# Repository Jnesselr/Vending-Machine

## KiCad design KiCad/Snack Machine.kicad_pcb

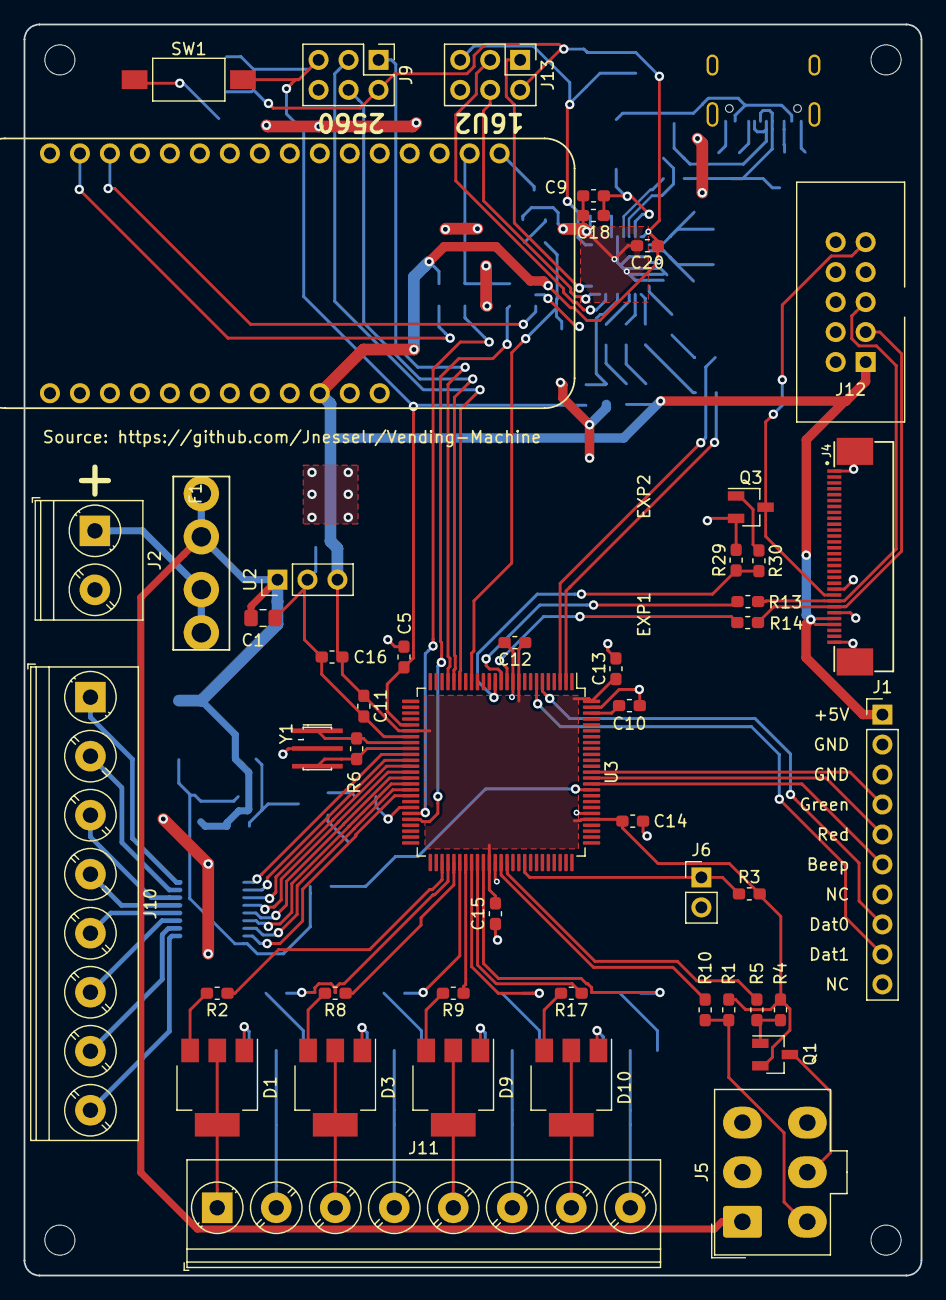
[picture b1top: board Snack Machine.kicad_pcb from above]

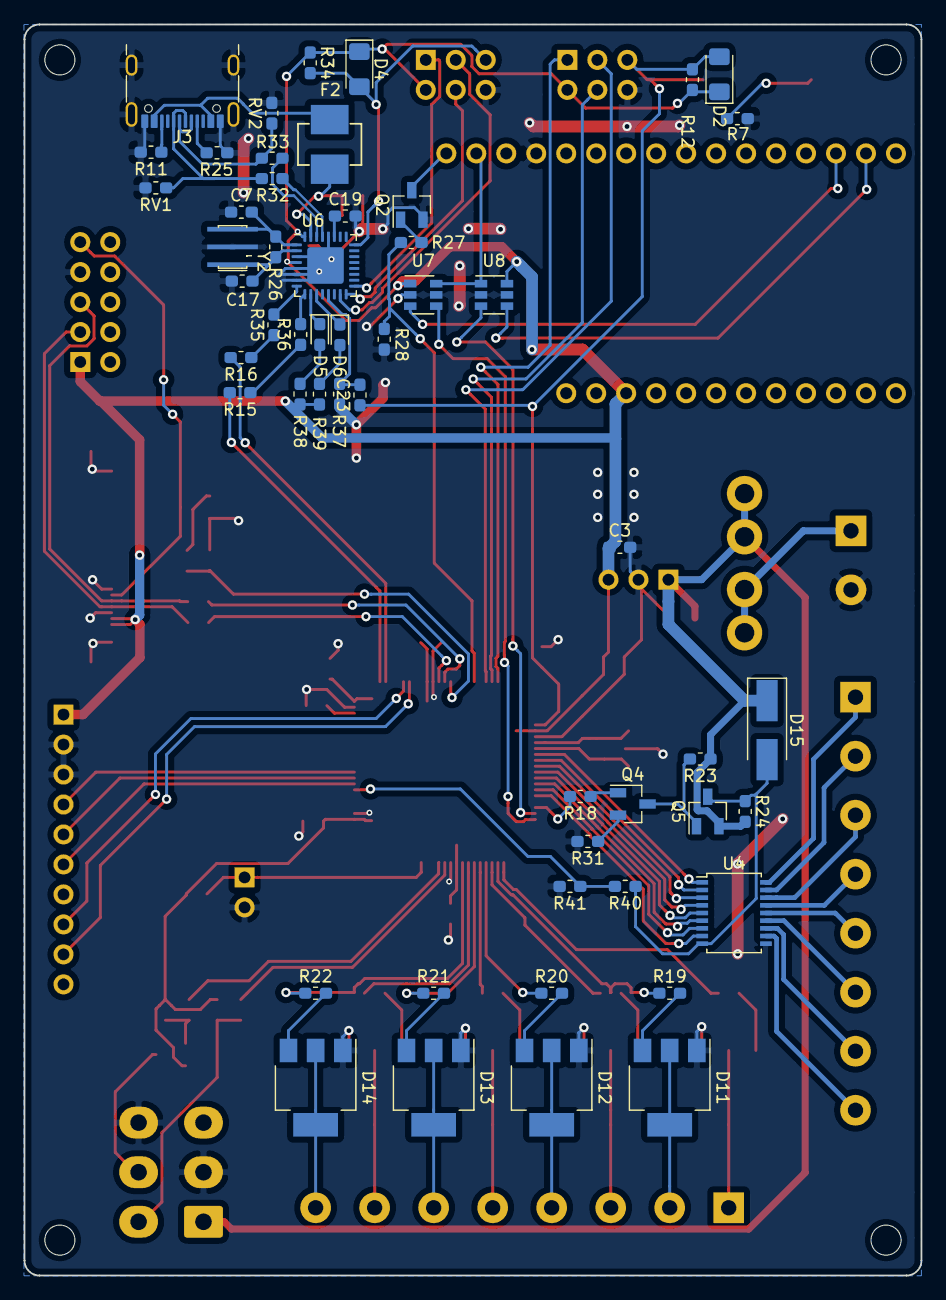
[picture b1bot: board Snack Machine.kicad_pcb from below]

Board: 2 copper layers, 76.0 x 106.0 mm, 105 parts (53 on the bottom side), 110 nets.

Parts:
C1: 2.2uF 35V; C_0805_2012Metric_Pad1.15x1.40mm_HandSolder
C3: 10uF 10V; C_0603_1608Metric_Pad1.05x0.95mm_HandSolder
C5, C7, C17: 22pF; C_0603_1608Metric_Pad1.05x0.95mm_HandSolder
C9, C10, C11, C12, C13, C14, C15, C23: 100nF; C_0603_1608Metric_Pad1.05x0.95mm_HandSolder
C16, C18, C19, C20: 1uF; C_0603_1608Metric_Pad1.05x0.95mm_HandSolder
D1, D3, D9, D10, D11, D12, D13, D14: Q_TRIAC_A1A2G; SOT-223-3_TabPin2
D2, D4: D; D_1206_3216Metric_Pad1.42x1.75mm_HandSolder
D5, D6: YELLOW; LED_0603_1608Metric_Pad1.05x0.95mm_HandSolder
D15: S1GTR; D_SMA_Handsoldering
F1: 1A; Keystone_3544-2
F2: 500mA; MF-MSMF050-2
J1: RFID_CONNECTOR; CONN_HEADER_VERT_10POS_2.54MM
J2: Power Screw Terminal; TerminalBlock_Phoenix_PT-1,5-2-5.0-H_1x02_P5.00mm_Horizontal
J3: USB_C_Receptacle_USB2.0; USB_C_Receptacle_HRO_TYPE-C-31-M-12
J4: V2 Display Ribbon Cable; FPC30
J5: MDB; Molex_Mini-Fit_Jr_5566-06A_2x03_P4.20mm_Vertical
J6: Conn_01x02; CONN_HEADER_VERT_2POS_2.54MM
J9, J13: AVR-ISP-6; PinHeader_2x03_P2.54mm_Vertical
J10: Row Screw Terminal; TerminalBlock_Phoenix_PT-1,5-8-5.0-H_1x08_P5.00mm_Horizontal
J11: Column Screw Terminal; TerminalBlock_Phoenix_PT-1,5-8-5.0-H_1x08_P5.00mm_Horizontal
J12: Display Serial Header; PinHeader_2x05_P2.54mm_Vertical
Q1, Q5: P-CH 30V 3.8A; SOT-23_Handsoldering_Lite
Q2, Q3, Q4: MMBT3904; SOT-23_Handsoldering_Lite
R1, R2, R5, R7, R8, R9, R17, R18, R19, R20, R21, R22, R35, R36, R37, R38, R39: 1k; R_0603_1608Metric_Pad1.05x0.95mm_HandSolder
R3, R4, R12, R23, R24, R34, R41: 10k; R_0603_1608Metric_Pad1.05x0.95mm_HandSolder
R6, R26: 1M; R_0603_1608Metric_Pad1.05x0.95mm_HandSolder
R10, R13, R14, R15, R16: 0R; R_0603_1608Metric_Pad1.05x0.95mm_HandSolder
R11, R25: 5k1; R_0603_1608Metric_Pad1.05x0.95mm_HandSolder
R27, R28, R29, R30, R31: 4.7k; R_0603_1608Metric_Pad1.05x0.95mm_HandSolder
R32, R33: 22R; R_0603_1608Metric_Pad1.05x0.95mm_HandSolder
R40: 47k; R_0603_1608Metric_Pad1.05x0.95mm_HandSolder
RV1, RV2: CG0603MLC; R_0603_1608Metric_Pad1.05x0.95mm_HandSolder
SW1: SW_SPST; SW_SPST_FSMSM
TH1, TH2, TH3, TH4: tooling_hole; tooling_hole_2.55
U2: MEZD71202A-G; mEZD71201A
U3: ATmega2560-16AU; TQFP-100_14x14mm_P0.5mm
U4: TBD62783A; SSOP-18_4.4x6.5mm_P0.65mm
U5: Huzzah32; HUZZAH32
U6: ATmega16U2-MU; QFN-32-1EP_5x5mm_P0.5mm_EP3.1x3.1mm
U7, U8: SN74LVC1T45DBV; SOT-23-6
Y1, Y2: 16MHz; Resonator_SMD_ECS-CR2-16.00-B-TR

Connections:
+3V3: U5.27, U7.6, U8.1
+5V: C3.1, C11.1, C12.1, C13.1, C14.1, C15.1, C16.1, C20.1, D2.1, D4.1, J1.1, J4.26, J4.27, J9.2, J12.1, J13.2, Q1.2, R1.2, R3.2, R4.2, R12.2, R34.1, R38.2, R39.2, U2.3, U3.10, U3.31, U3.61, U3.80, U3.100, U5.3, U6.4, U6.32, U7.1, U8.6
+24V: C1.1, D15.1, F1.1, J5.1, Q5.2, R23.1, R24.2, U2.1
/4D_Display/DISPLAY_RX: J4.23, J12.5, R13.2
/4D_Display/DISPLAY_TX: J4.24, J12.3, R14.2
/4D_Display/RESET: J4.22, J12.9, Q3.3
/DISPLAY_RX_MEGA_TX: R13.1, U3.13
/DISPLAY_TX_MEGA_RX: R14.1, U3.12
/DOOR_SW: J6.1, R3.1, U3.67
/HUZZAH_RX_MEGA_TX: U3.46, U7.4
/HUZZAH_TX_MEGA_RX: U3.45, U8.3
/MDB_RX: Q1.1, R4.1, R5.1
/MDB_RX_MEGA_TX: R5.2, U3.64
/MDB_TX: J5.4, R1.1, R10.1
/MDB_TX_MEGA_RX: R10.2, U3.63
/MISO: J9.1, U3.22
/MOSI: J9.4, U3.21
/MOTORS_ENABLE: R18.2, U3.44
/MOTOR_SENSE: R40.2, R41.1, U3.85
/MotorPower/col_1_motor: D1.2, J11.1
/MotorPower/col_2_motor: D11.2, J11.2
/MotorPower/col_3_motor: D3.2, J11.3
/MotorPower/col_4_motor: D12.2, J11.4
/MotorPower/col_5_motor: D9.2, J11.5
/MotorPower/col_6_motor: D13.2, J11.6
/MotorPower/col_7_motor: D10.2, J11.7
/MotorPower/col_8_motor: D14.2, J11.8
/MotorPower/row_a_motor: J10.1, U4.18
/MotorPower/row_b_motor: J10.2, U4.17
/MotorPower/row_c_motor: J10.3, U4.16
/MotorPower/row_d_motor: J10.4, U4.15
/MotorPower/row_e_motor: J10.5, U4.14
/MotorPower/row_f_motor: J10.6, U4.13
/MotorPower/row_g_motor: J10.7, U4.12
/MotorPower/row_h_motor: J10.8, U4.11
/RESET_DISPLAY: R29.1, R30.2, U3.14
/RESET_HUZZAH: R27.2, R28.1, U3.18
/RFID_BEEP_CTRL: J1.6, U3.86
/RFID_DATA_0: J1.8, U3.6
/RFID_DATA_1: J1.9, U3.7
/RFID_GREEN_LED: J1.4, U3.88
/RFID_RED_LED: J1.5, U3.87
/SCK: J9.3, U3.20
/USB_Serial/DTR: C23.2, R37.2, U6.13
/USB_Serial/MICRO_D+: R32.1, U6.29
/USB_Serial/MICRO_D-: R33.1, U6.30
/USB_Serial/MISO2: J13.1, U6.17
/USB_Serial/MOSI2: J13.4, U6.16
/USB_Serial/RXL: D5.1, U6.10
/USB_Serial/RX_USB: R16.1, R35.1
/USB_Serial/SCK2: J13.3, U6.15
/USB_Serial/TXL: D6.1, U6.11
/USB_Serial/TX_USB: R15.1, R36.1
/USB_Serial/USBVCC: C9.1, C18.1, F2.1, U6.31
/USB_Serial/USB_D+: J3.A6, J3.B6, R32.2, RV1.1
/USB_Serial/USB_D-: J3.A7, J3.B7, R33.2, RV2.1
/USB_Serial/XVCC: F2.2, J3.A4, J3.B4
/USB_Serial/~RESET2: D4.2, J13.5, R34.2, U6.24
/XTAL1: R6.1, U3.34, Y1.3
/XTAL2: R6.2, U3.33, Y1.1
/c1: R2.1, U3.53
/c2: R19.1, U3.54
/c3: R8.1, U3.55
/c4: R20.1, U3.56
/c5: R9.1, U3.57
/c6: R21.1, U3.58
/c7: R17.1, U3.59
/c8: R22.1, U3.60
/r1: U3.35, U4.1
/r2: U3.36, U4.2
/r3: U3.37, U4.3
/r4: U3.38, U4.4
/r5: U3.39, U4.5
/r6: U3.40, U4.6
/r7: U3.41, U4.7
/r8: U3.42, U4.8
/~RESET: C5.1, C23.1, D2.2, J9.5, R12.1, SW1.2, U3.30
GND: C1.2, C3.2, C5.2, C7.1, C9.2, C10.2, C11.2, C12.2, C13.2, C14.2, C15.2, C16.2, C17.1, C18.2, C19.2, C20.2, D1.1, D3.1, D9.1, D10.1, D11.1, D12.1, D13.1, D14.1, J1.2, J1.3, J2.2, J3.A1, J3.B1, J3.S1, J4.1, J4.21, J4.25, J4.30, J4.MP, J5.2, J5.6, J6.2, J9.6, J12.7, J13.6, Q2.2, Q3.2, R7.1, R11.2, R25.2, R28.2, R29.2, R31.2, R37.1, R41.2, RV1.2, RV2.2, U2.2, U3.11, U3.32, U3.62, U3.81, U3.99, U4.10, U5.25, U6.3, U6.5, U6.6, U6.7, U6.28, U6.33, U7.2, U7.5, U8.2, U8.5, Y1.2, Y2.2
unnamed: C7.2, R26.1, U6.1, Y2.3
unnamed: C10.1, U3.98
unnamed: C17.2, R26.2, U6.2, Y2.1
unnamed: C19.1, U6.27
unnamed: D1.3, R2.2
unnamed: D3.3, R8.2
unnamed: D5.2, R38.1
unnamed: D6.2, R39.1
unnamed: D9.3, R9.2
unnamed: D10.3, R17.2
unnamed: D11.3, R19.2
unnamed: D12.3, R20.2
unnamed: D13.3, R21.2
unnamed: D14.3, R22.2
unnamed: D15.2, Q5.3, R24.1, R40.1, U4.9
unnamed: F1.2, J2.1
unnamed: J3.A5, R25.1
unnamed: J3.B5, R11.1
unnamed: J5.5, Q1.3
unnamed: Q2.1, R27.1
unnamed: Q2.3, U5.28
unnamed: Q3.1, R30.1
unnamed: Q4.1, R18.1
unnamed: Q4.2, R31.1
unnamed: Q4.3, Q5.1, R23.2
unnamed: R7.2, SW1.1
unnamed: R15.2, U3.2
unnamed: R16.2, U3.3
unnamed: R35.2, U6.8
unnamed: R36.2, U6.9
unnamed: U5.14, U8.4
unnamed: U5.15, U7.3

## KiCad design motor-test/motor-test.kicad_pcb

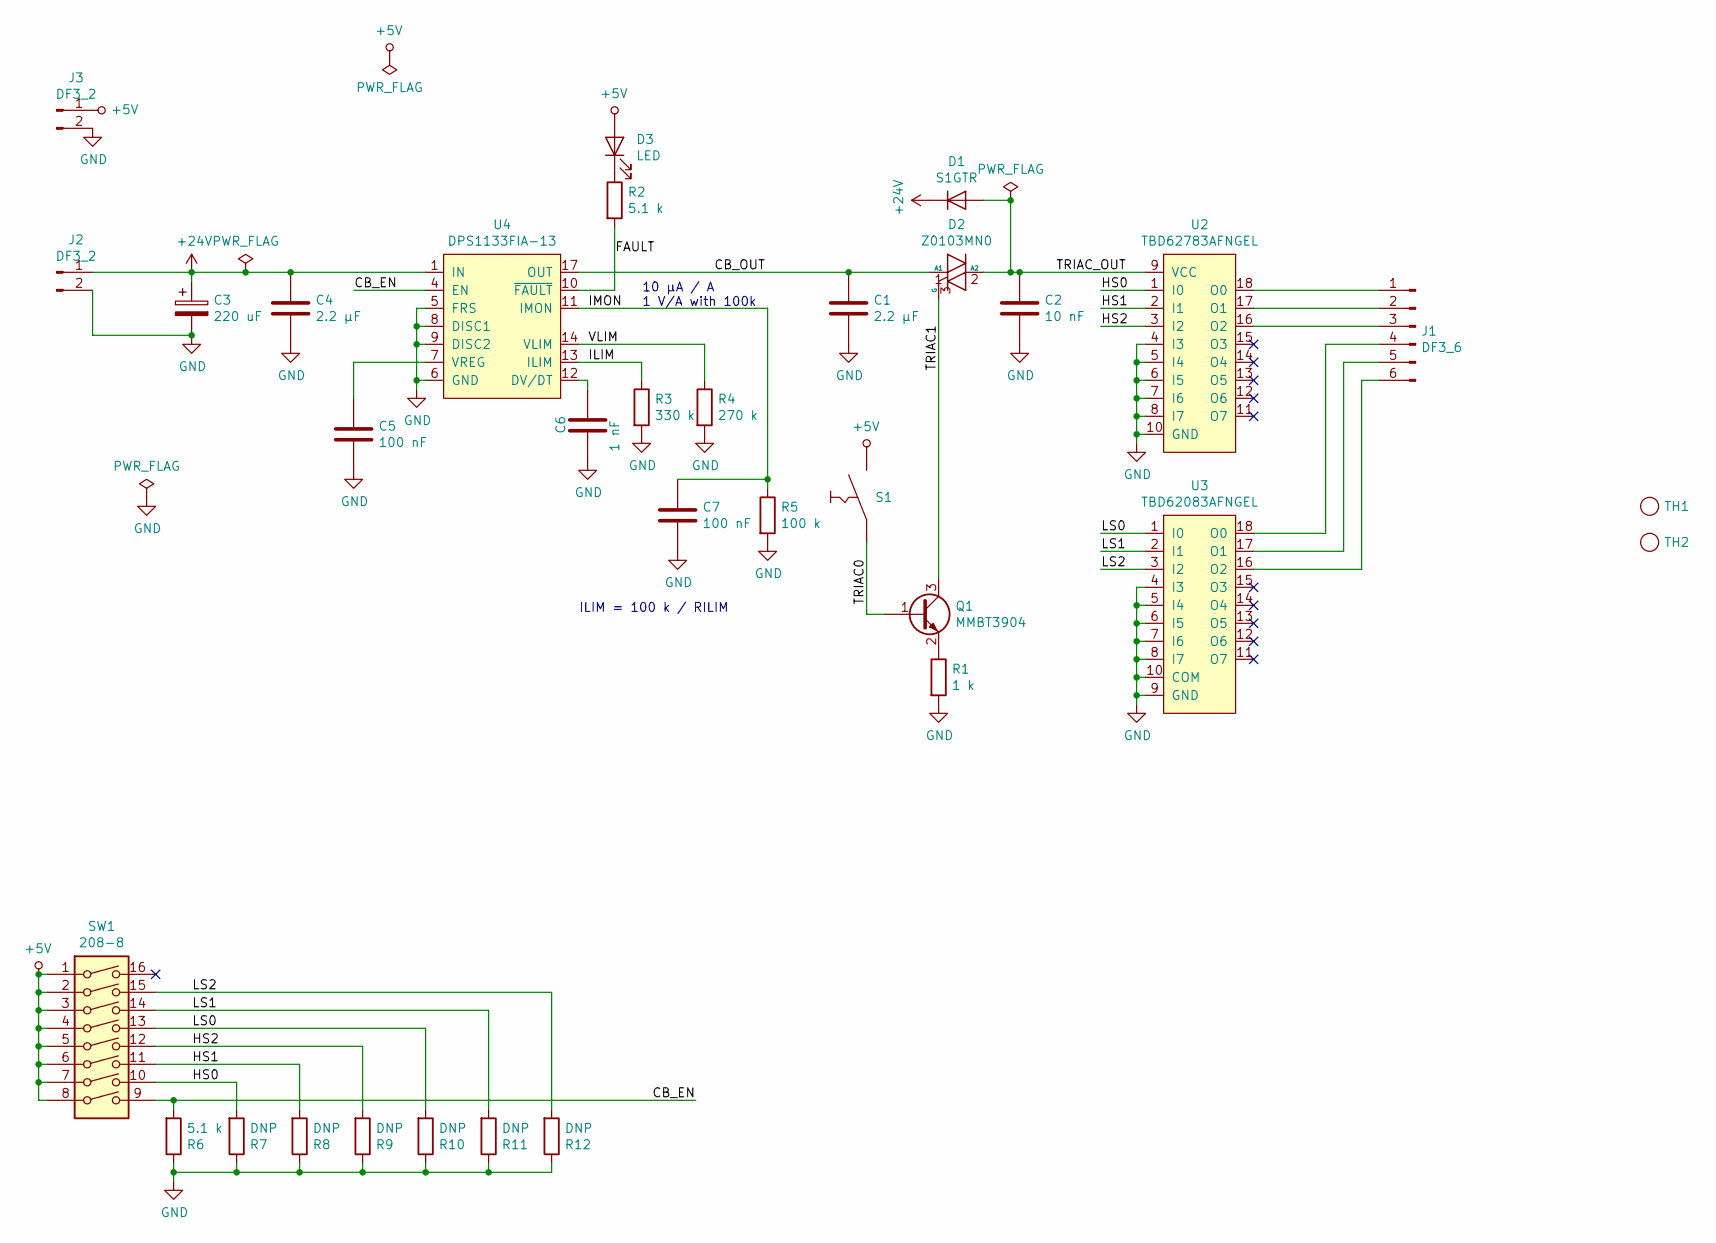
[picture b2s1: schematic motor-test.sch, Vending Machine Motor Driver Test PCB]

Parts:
C1, C4: 2.2 μF; C_0603_1608Metric
C2: 10 nF; C_0603_1608Metric
C3: 220 uF; CP_Radial_D10.0mm_P5.00mm
C5, C7: 100 nF; C_0603_1608Metric
C6: 1 nF; C_0603_1608Metric
D1: S1GTR; D_SMA
D2: Z0103MN0; SOT-223-3_TabPin2
D3: LED; LED_0603_1608Metric
J1: DF3_6
J2, J3: DF3_2
Q1: MMBT3904; SOT-23
R1: 1 k; R_0603_1608Metric
R2, R6: 5.1 k; R_0603_1608Metric
R3: 330 k; R_0603_1608Metric
R4: 270 k; R_0603_1608Metric
R5: 100 k; R_0603_1608Metric
R7, R8, R9, R10, R11, R12: DNP; R_0603_1608Metric
S1: 147873-1; PB_3.5x6
SW1: 208-8; DIP-16_W7.62mm
TH1, TH2: tooling_hole; tooling_hole_2.55
U2: TBD62783AFNGEL; SSOP-18_4.4x6.5mm_P0.65mm
U3: TBD62083AFNGEL; SSOP-18_4.4x6.5mm_P0.65mm
U4: DPS1133FIA-13; QFN-17-Diodes1

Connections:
+5V: D3.2 (A), J3.1, S1.2, SW1.1, SW1.2, SW1.3, SW1.4, SW1.5, SW1.6, SW1.7, SW1.8
+24V: C3.1, C4.1, D1.1 (K), J2.1, U4.1 (IN)
/CB_EN: R6.2, SW1.9, U4.4 (EN)
/CB_OUT: C1.1, D2.1 (A1), U4.17 (OUT)
/FAULT: R2.2, U4.10 (~FAULT)
/HS0: R7.2, SW1.10, U2.1 (I0)
/HS1: R8.2, SW1.11, U2.2 (I1)
/HS2: R9.2, SW1.12, U2.3 (I2)
/ILIM: R3.1, U4.13 (ILIM)
/IMON: C7.1, R5.1, U4.11 (IMON)
/LS0: R10.2, SW1.13, U3.1 (I0)
/LS1: R11.2, SW1.14, U3.2 (I1)
/LS2: R12.2, SW1.15, U3.3 (I2)
/TRIAC0: Q1.1 (B), S1.1
/TRIAC1: D2.3 (G), Q1.3 (C)
/TRIAC_OUT: C2.1, D1.2 (A), D2.2 (A2), U2.9 (VCC)
/VLIM: R4.1, U4.14 (VLIM)
GND: C1.2, C2.2, C3.2, C4.2, C5.2, C6.2, C7.2, J2.2, J3.2, R1.2, R3.2, R4.2, R5.2, R6.1, R7.1, R8.1, R9.1, R10.1, R11.1, R12.1, U2.4 (I3), U2.5 (I4), U2.6 (I5), U2.7 (I6), U2.8 (I7), U2.10 (GND), U3.4 (I3), U3.5 (I4), U3.6 (I5), U3.7 (I6), U3.8 (I7), U3.9 (GND), U3.10 (COM), U4.5 (FRS), U4.6 (GND), U4.8 (DISC1), U4.9 (DISC2)
unnamed: C5.1, U4.7 (VREG)
unnamed: C6.1, U4.12 (DV/DT)
unnamed: D3.1 (K), R2.1
unnamed: J1.1, U2.18 (O0)
unnamed: J1.2, U2.17 (O1)
unnamed: J1.3, U2.16 (O2)
unnamed: J1.4, U3.18 (O0)
unnamed: J1.5, U3.17 (O1)
unnamed: J1.6, U3.16 (O2)
unnamed: Q1.2 (E), R1.1

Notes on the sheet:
10 μA / A 1 V/A with 100k
ILIM = 100 k / RILIM

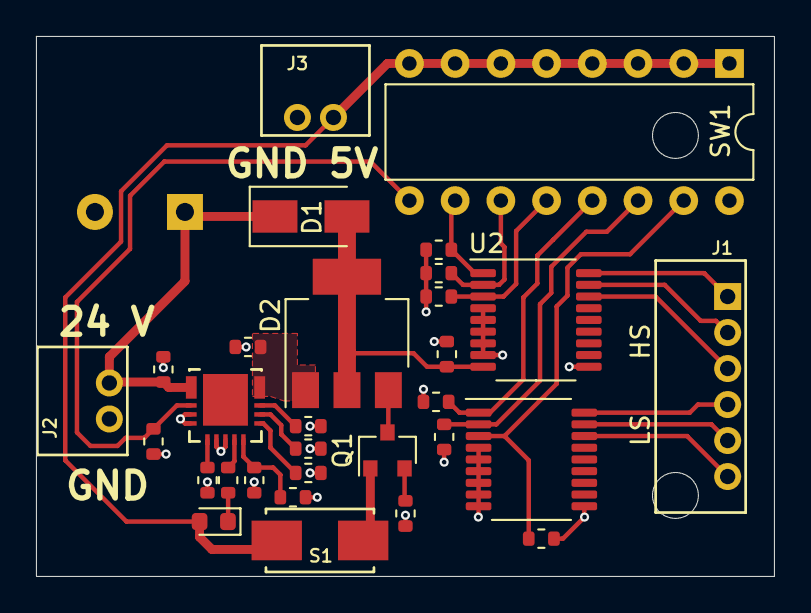
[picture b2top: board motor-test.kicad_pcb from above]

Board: 2 copper layers, 41.0 x 30.0 mm, 33 parts (1 on the bottom side), 28 nets.

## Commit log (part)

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2018-10-16 Improving motor high side schematic and making it more generalized
2018-10-16 Switching to +5V from vcc
2018-10-16 Adding USB Serial page and fixing address pins in INA219
2018-10-16 Adding mdb interface ports
2018-11-08 first stab at changes, added switching power supply, updated 2 ATmega footprints per KiCAD 5.0.2 update
2018-11-19 Large number of changes, some cosmetic, most functional. Added analog current sense circuit, added switching power supply (24V->5V), added switch connector for sensing when door is open, added LCD128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
2018-11-20 small tweaks
2018-11-27 Updating gitignore for datasheets and reqs.txt
2018-11-27 Updating annotations for all schematics
2018-11-27 latest changes, mostly test points and annotations
2018-11-27 changed all mosfets
2018-11-27 Added input and output caps to 3.3V regulator
2018-11-27 Adding cache library to git ignore
2018-11-28 Annotating schematic
2018-11-28 Adding more footprints
2018-11-29 First crack at a layout
2018-12-02 Way too much work to accurately describe in a commit message
2018-12-02 Pushing up current changes
2018-12-11 added parts for Y3, FB2, FB3, F1
2018-12-11 added note about MDB needing opto-isolation
2018-12-20 Fixing small issue with a missing $EndComp
2018-12-20 removed D1 and D3, left Schottky diodes alone
2018-12-20 tweaked ethernet
2018-12-20 created footprint for USB micro, linked to J16
2018-12-20 fixed W5500 schematic part
2018-12-22 updated motor drive circuitry, annotated
2018-12-22 imported netlist
2018-12-28 changed footprints for SMB and SOT-23 so the handsoldering is more reasonable
2018-12-28 changed footprint for TSOT23 handsoldering to be more reasonable
2018-12-28 added one resistor, about to rip up all traces and move all the parts around
2018-12-28 moving stuff around
2018-12-31 all parts placed within board outline
2018-12-31 some routing complete
2019-01-01 pushing stuff around, routing more
2019-01-04 changed SW1 footprint, generated netlist
2019-01-05 all nets routed, reference designators aligned
2019-01-05 tweaked
2019-01-08 added BOM first draft
2019-01-15 starting new branch to whack ethernet, replace with ESP32
2019-01-15 Removing CSV exemption from .gitignore
2019-01-15 changed C1 to 0805
2019-01-24 Added ESP32 Huzzah module and logic level converters. Looks like TX and RX need to be checked for all UARTs on ATmega2560. Also, some of the Q and R reference designators reverted to ? in the motor d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
2019-01-25 Trying to fix label errors
2019-01-26 Adding HUZZAH32 footprint
2019-02-01 fixed UARTs on Mega2560
2019-02-01 imported new netlist
2019-02-01 pushed a couple of reference designators, fixed copper pours
2019-02-03 Updating a ton of part numbers
2019-02-03 Fixing small typo
2019-02-27 Basic framework for multiple configs
2019-02-27 Initial firmware commit
2019-02-27 Cleaning up function usage
2019-03-06 Added library cache
2019-07-17 add motor test
2019-07-24 change component values to available ones
2019-08-09 Added MIT license file
2019-12-09 Missing annotations
2019-12-09 Fixing ERC rules
2019-12-09 Combining RFID to 1 header and improving 4D LCD stuff
2019-12-09 Rotated serial ports around to make routing easier
2019-12-09 Committing before changing schematic
2019-12-09 Unrouted is 0! Woot!
2019-12-09 Sourcing parts
2019-12-09 Adding source to SilkScreen
2019-12-31 Added part number, manufacturer, and personal bin numbers
2019-12-31 Cleaning up the state machine a little bit
2019-12-31 A little more cleanup
2019-12-31 Ring buffer is now a template
2019-12-31 Switching to Eventually for event management
2019-12-31 Refactored a little bit to make listeners easier
2019-12-31 Expanding out most of the level 2 coin chaner functionality
2019-12-31 Committing current progress on RFID work
2019-12-31 Refactoring a lot of the MDB code to be easier to use hopefully
2020-02-09 Getting motors to start turning
2020-02-09 Platform IO now knows about the wifi bridge too
2020-04-09 Updating board to remove EXP1/EXP2
2020-04-09 Improving some grounding issues
2020-05-02 Committing changes to the circuit board
2020-05-17 Getting product info from the website
2020-05-24 Working on the rest requests
2020-05-25 Bridge can update order now
2020-05-25 Added debug, credit amount control, and auth
2020-05-25 Fixing compile error
2020-05-27 Fixing a couple of small issues
2020-07-11 Adding code to control motors
2020-07-14 Removing Eventually in favor of a custom solution
2020-07-15 Committing while it works
2020-07-25 Removing more logs
2020-07-26 Bringing all hardware online at the same time
    - Had to fix some timing issues in this diff
2020-07-26 Got Site Link handshake to work
2020-07-26 Refactored out some methods for the site link
2020-07-27 Added get order by card works
2020-07-27 Testing out some WindowManager stuff
2020-07-27 WindowManager now has width/height from the screen
2020-07-27 Cleaning task timing a little bit
2020-07-29 Adding watchdog timer and fun MainWindow test
2020-07-29 Basic boot screen works now
2020-07-30 Improved screen startup time
2020-07-31 Switched draw -> show and added hiding Window method
2020-07-31 Added touch screen functionality in WindowManager
2020-08-01 Added some buttons for the letters and numbers
2020-08-01 Got a nice basic keyboard layout going for choosing item
2020-08-01 Fixing some issues with the API and with compiling the wifi bridge
2020-08-01 Refactored out Product class
2020-08-01 Added ProductManager to keep up with products and stock in machine
2020-08-01 Fixing some wifi bridge issues
2020-08-01 Small fix in SiteLink
    I thought I could make it handle the reset slightly faster but
    lowering how many loops it took to cause a reset meant it would
    reset infinitely.
2020-08-01 ProductManager can now fetch via product id
2020-08-01 Session now has current order
2020-08-01 Improving SiteLink reliability a little more
2020-08-02 Added basic proof of concept available and total money
2020-08-02 Added a bunch of callbacks for the BillValidator
2020-08-02 Added Cancel Button
2020-08-02 Refactored MainWindow code to be a bit easier to manage
2020-08-02 Improving look of cancel order button a little
2020-08-02 Clicking "Cancel Order" resets current session
2020-08-02 Slightly improved output of monies
2020-08-03 Started with Membership Button
2020-08-03 Membership Button now shows orders available for pickup
2020-08-03 Added ability to tap on orders grabbed from the internet
2020-08-03 Finished refactoring callbacks
2020-08-03 Fixing small issue with Membership Button
2020-08-03 Host side now ACKs in SiteLink
2020-08-03 Order status gets sent over wifi bridge
2020-08-03 SiteLink now correctly grabs order status
2020-08-03 Trying to fix/improve button management in MainWindow
2020-08-03 Handling unknown card scan
    Also changed the colors of the vend button around so it's more
    visible when you can vend
2020-08-05 Added "Get Credit by Card" functionality
2020-08-05 Improving SiteLink protocol slightly
    This diff does two things. First we reduce the size of a product update
    by shortening the max length of the name. This ensures that the max product
    packet length is 63 bytes.
    The second thing it does is not send product updates unless the host requests
    it. This is to work around some of the issues with ACKing packets.
2020-08-05 Adjusting how ACKs work for fetching orders
    This is to help prevent buffer overflowing and will be one of several
    diffs like it. The basic concept is, if the next piece of the packet,
    whether it's the order header, item, etc. would overflow the buffer,
    then we wait for an ACK from the other side. Both sides use the same
    math so the ACK and wait for ACK on the same schedule.
2020-08-06 Update order now sends ACK at the correct times
2020-08-06 Get order for SiteLink sends ACKs correctly now
2020-08-06 Refactored order processing to work with new ACK paradigm
2020-08-06 Added "update credit by card" endpoint to SiteLink
2020-08-06 Refactored SiteLinkAck out of the SiteLink class
    The SiteLink will have "update order" added soon and that means
    it needs some of the ACK stuff available outside the SiteLink class.
2020-08-06 Getting started on the update order endpoint
2020-08-06 Added "Update Order" endpoint
    No idea of it works currently. I'll need to build out some test data
    for it and then test it, so this may not work 100% but we'll see.
2020-08-06 Vending existing processed order seems to work now
2020-08-06 Inverted the colors on the main window buttons
    I originally made the buttons have the color border and the white
    background when not pressed and then switched to one solid color
    with white text when pressed. This diff inverts that.
    If someone is colorblind then the enabled not-pressed button and
    the disabled button would look basically the same. Plus this
    honestly just looks better with the pressed action. In real life
2020-08-06 Full vend functionality works
    It's very basic and doesn't handle corner cases, but it was very
    cool to watch the order update to the 'processing' status and then
    update to the 'vending' status.
    I still haven't done this with it all installed in the machine, so
    no idea if it actually turns the motors with this version. We've
    made some heavy modifications to that class since the last test.
2020-08-07 CoinChanger can now dispense arbitrary amounts
2020-09-24 Fixing a couple of small timing issues
2020-09-24 Cancelling order now dispenses change on cardless orders
2020-09-24 Fixed a couple of corner cases around change management
2020-09-24 Not letting customer add more stock than we have
2020-09-24 Limiting order to 8 unique items
2020-09-25 Fixing a couple of small bugs
2020-10-17 Fixing a couple of small issues that have been found
    - The screen wasn't clearing everything if you had too many items on screen
    - Sometimes things like card scanning and product updates stopped working.
    Best guess is the two boards got out of sync so now the main board sends a
    reset on the secondary board if it's not safe to send from the main board's
    perspective but the huzzah32 hasn't responded yet
2021-02-07 untracked files on rev4: f443c88 Preventing vend issue with last item available
2021-02-11 Automatically reset the board in case of issues
2021-02-11 Revert "untracked files on rev4: f443c88 Preventing vend issue with last item available"
    This reverts commit 96ae08953e1a785916d74f2d1b476cea8e7f1401.
2021-02-18 Added serial message if item isn't valid
2021-05-29 Added RFID/CC link implementation code
2021-05-29 Trying to debug rfid cc
2023-01-16 Preventing copy overwriting reset order
2023-01-16 Updated MDB code to use only one copy of MDBResult
2023-01-19 Small changes to remove unused code / fix comments
2023-01-30 Removed GizmoDojo config since they no longer have a vending machine
2023-01-30 Fixing issue with SiteLinkCommand coppy constructor
2023-01-30 Updated UI for main window a bit
2023-01-30 Shorter boot timeout and faster baud rate
2023-01-30 Removed a bunch of debug output
2023-02-19 Moved Screen setup into its own class
2023-02-19 Windows are now static classes
2023-03-04 Moving Main Board down one level
2024-09-15 Updated upload port for esp32i
2024-09-15 Fixed progress bar being written to a different location
2024-09-15 Added timeout for active session
2024-09-15 Boot window checks denhac.org connection
